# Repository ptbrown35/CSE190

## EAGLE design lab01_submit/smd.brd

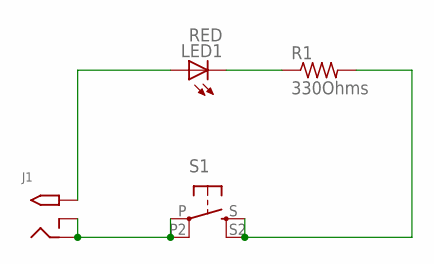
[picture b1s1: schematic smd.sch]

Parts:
J1: 2.1MMJACKTHM; PJ-102A
LED1: RED; LED5MM
R1: 330Ohms; RESAD1160W55L680D260_HS
S1: BUTTON-TACTILE-SMD

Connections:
unnamed: J1.TIP, LED1.A
unnamed: LED1.K (C), R1.1
unnamed: R1.2, S1.S, S1.S2 (S1)
unnamed: J1.RING, J1.RING_SW, S1.P, S1.P2 (P1)

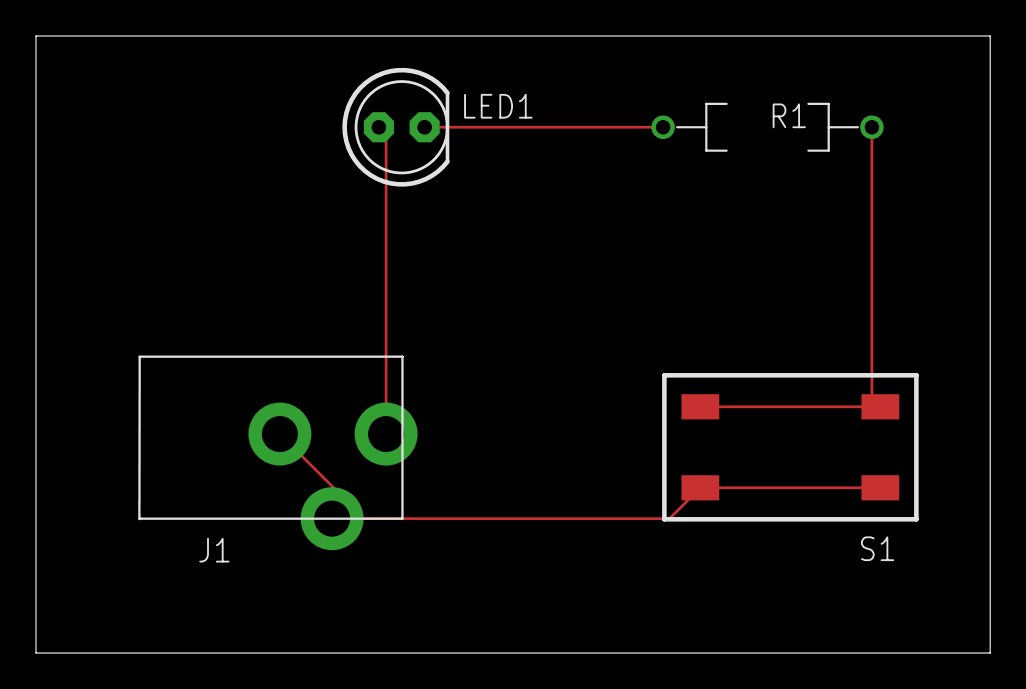
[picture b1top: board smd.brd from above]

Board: 4 copper layers, 53.0 x 34.3 mm, 4 parts (0 on the bottom side), 4 nets.

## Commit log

2018-04-04 lab01
2018-04-04 lab01 v2
2018-04-04 lab01 v3
